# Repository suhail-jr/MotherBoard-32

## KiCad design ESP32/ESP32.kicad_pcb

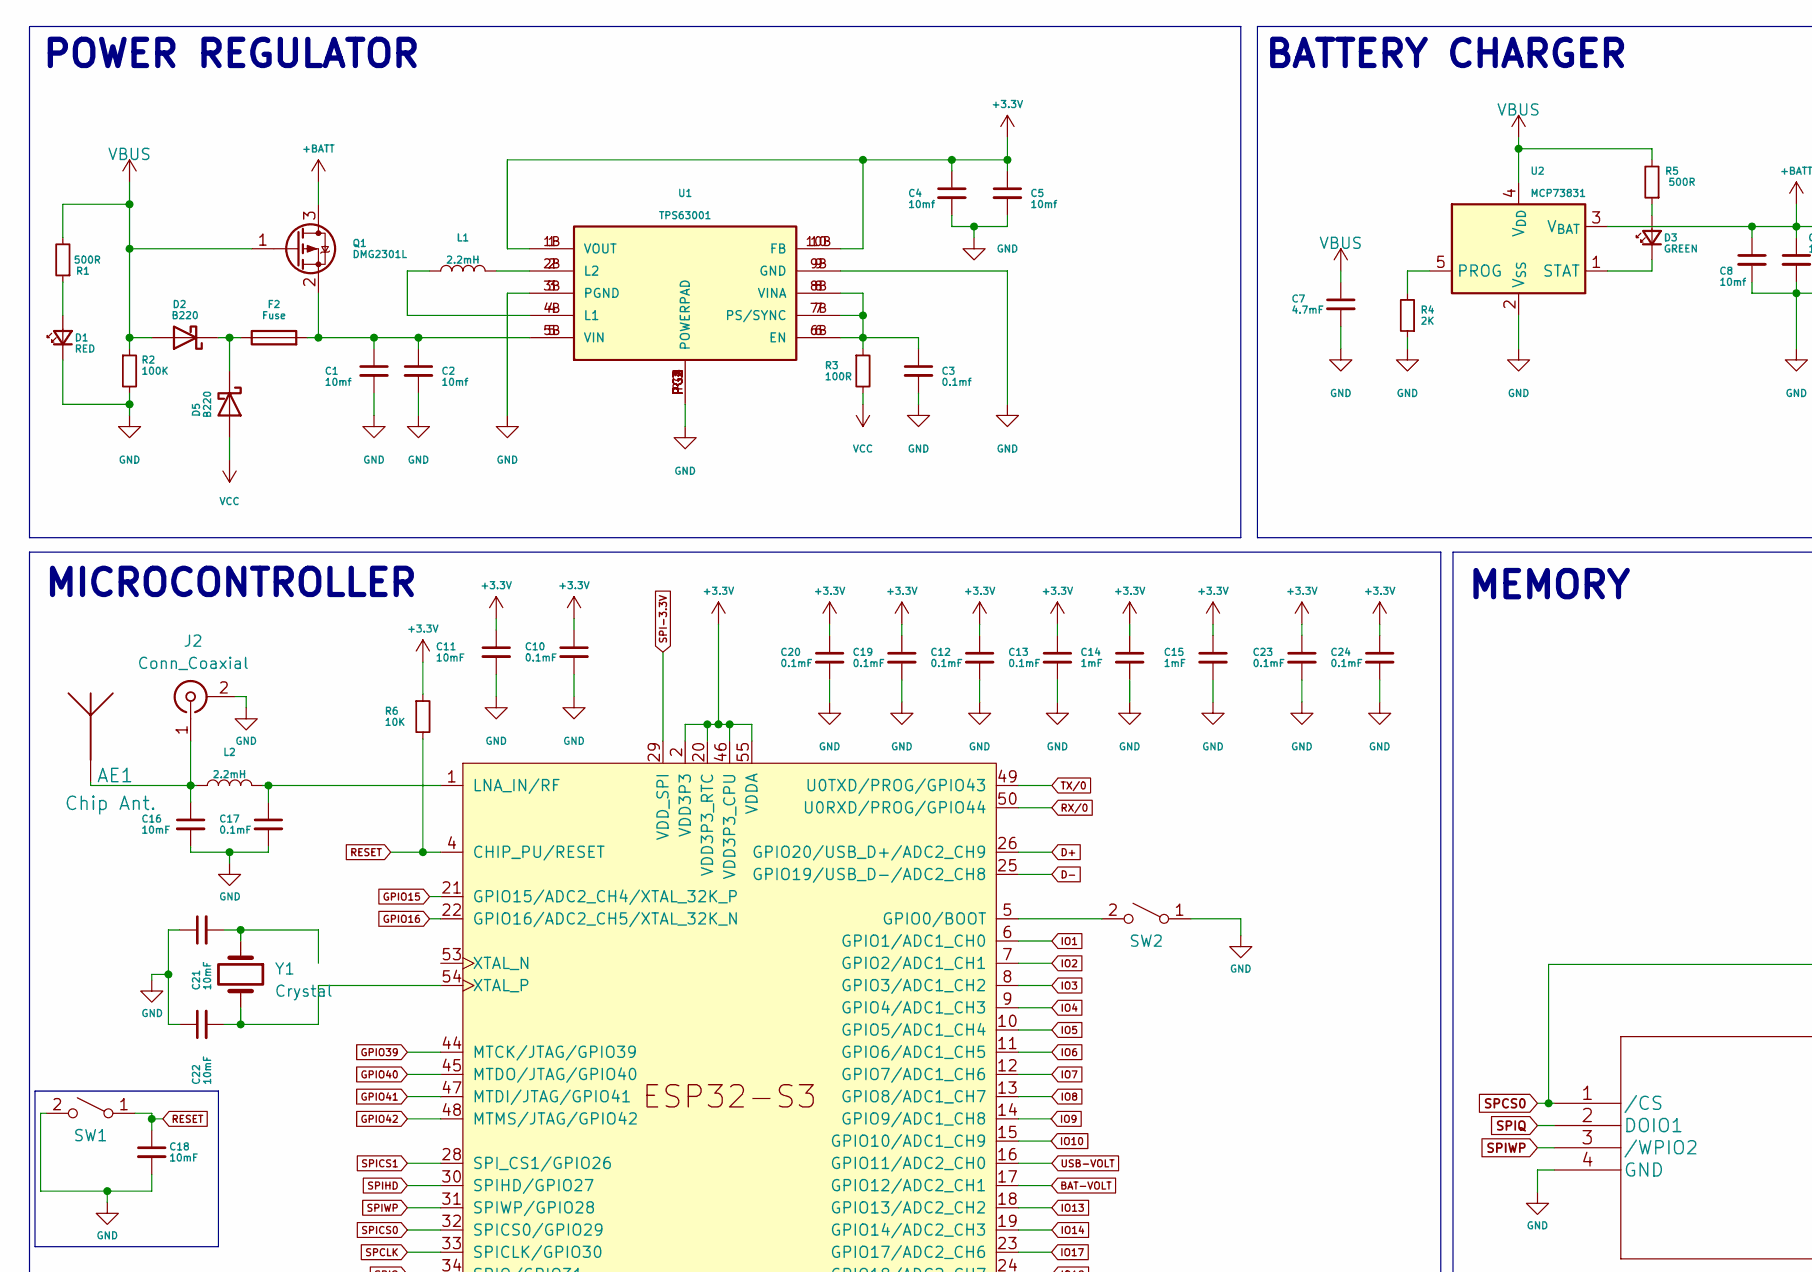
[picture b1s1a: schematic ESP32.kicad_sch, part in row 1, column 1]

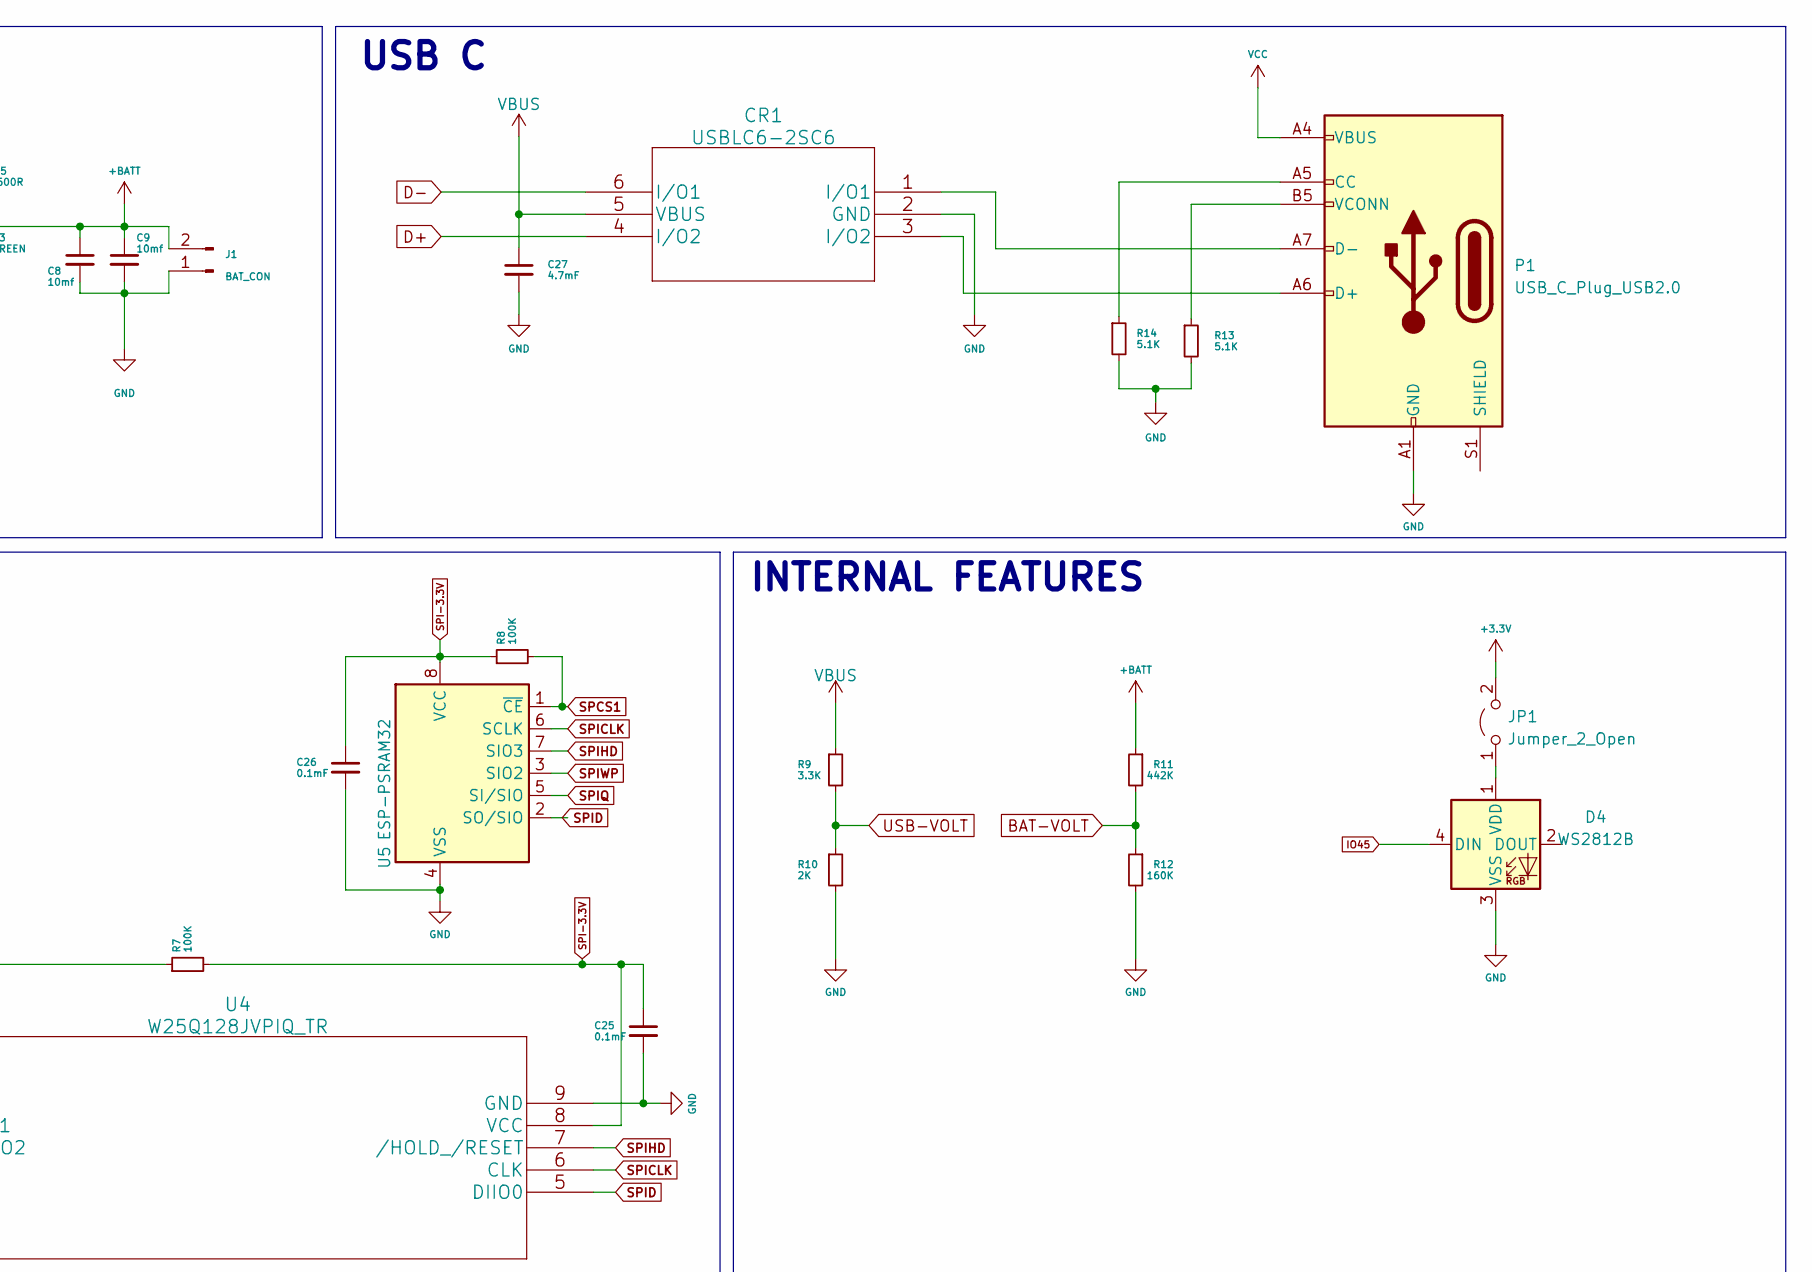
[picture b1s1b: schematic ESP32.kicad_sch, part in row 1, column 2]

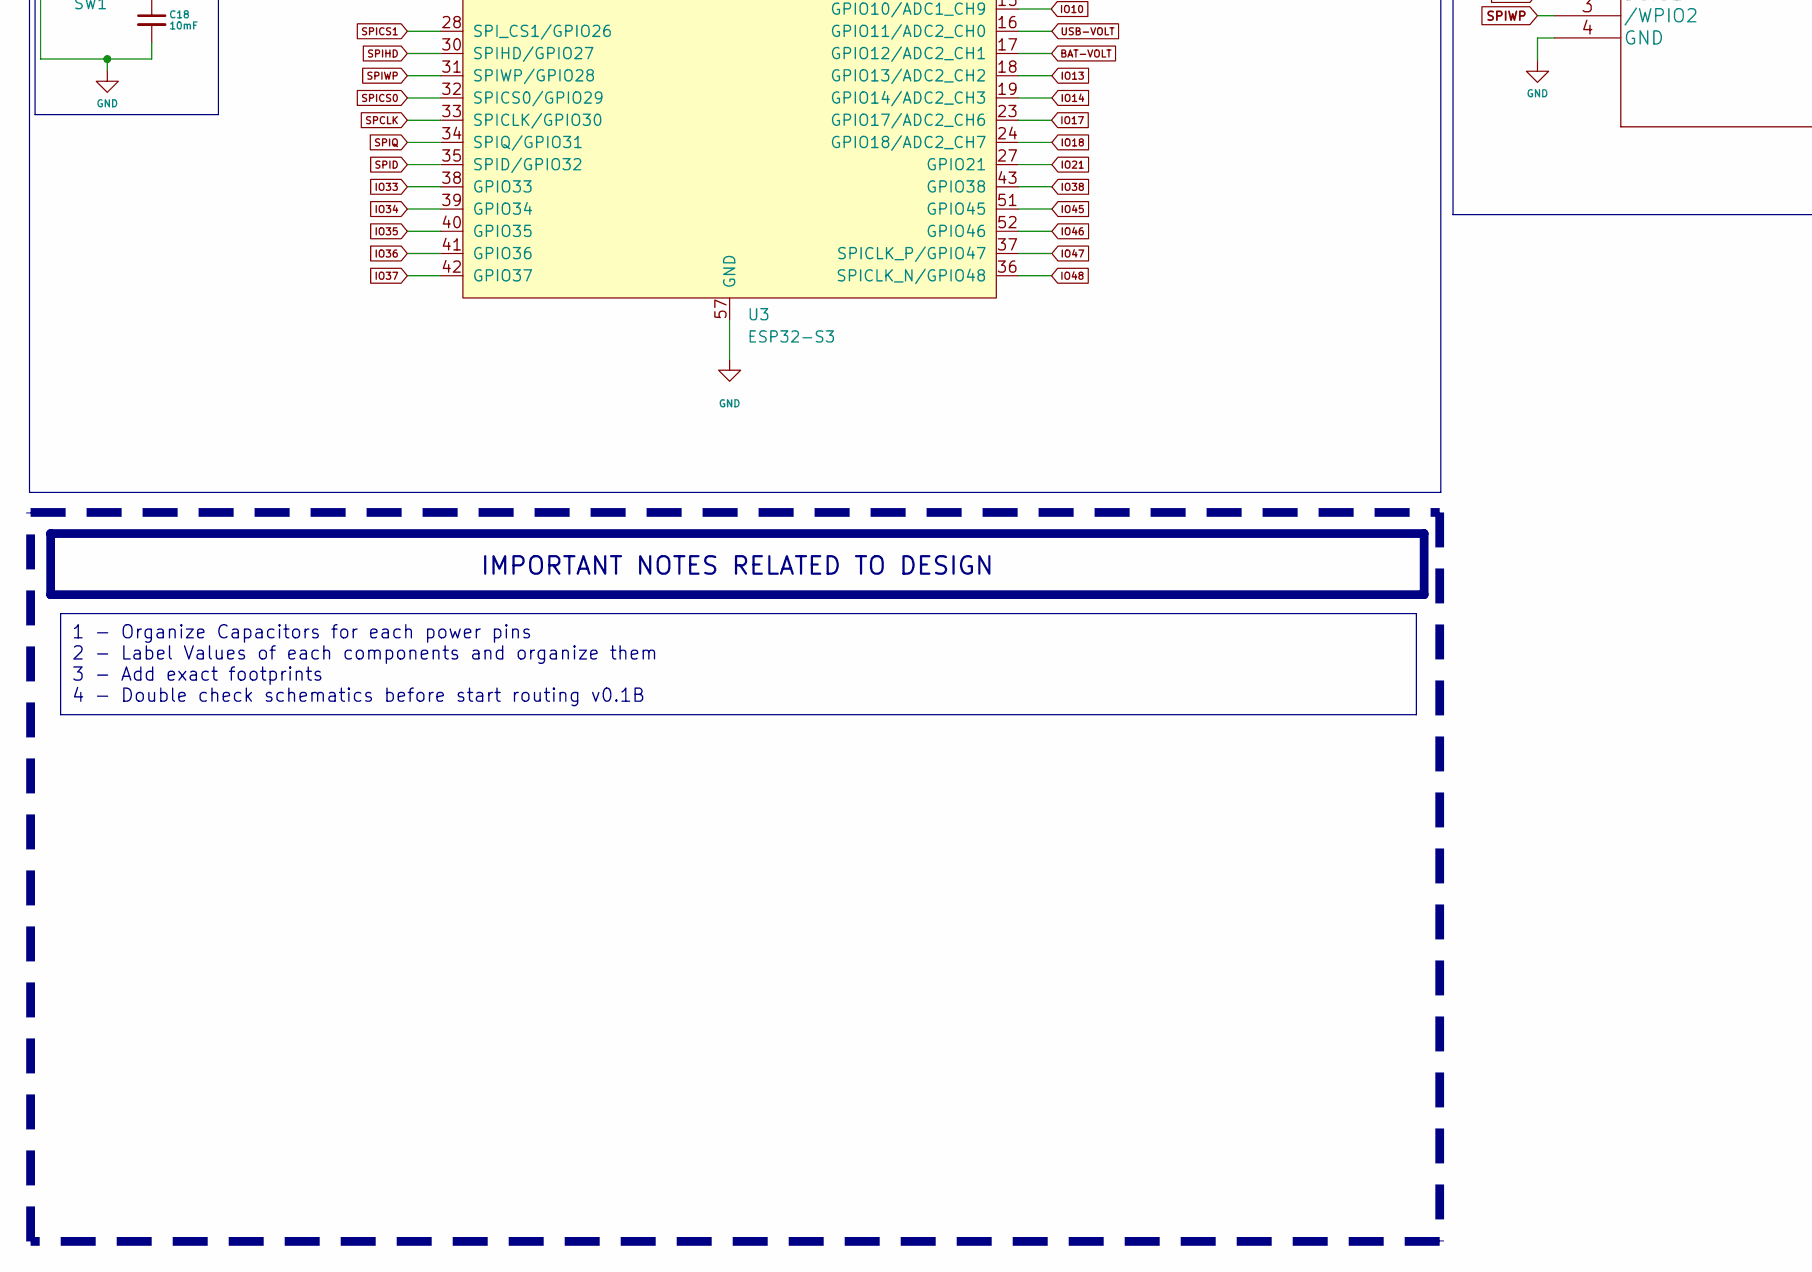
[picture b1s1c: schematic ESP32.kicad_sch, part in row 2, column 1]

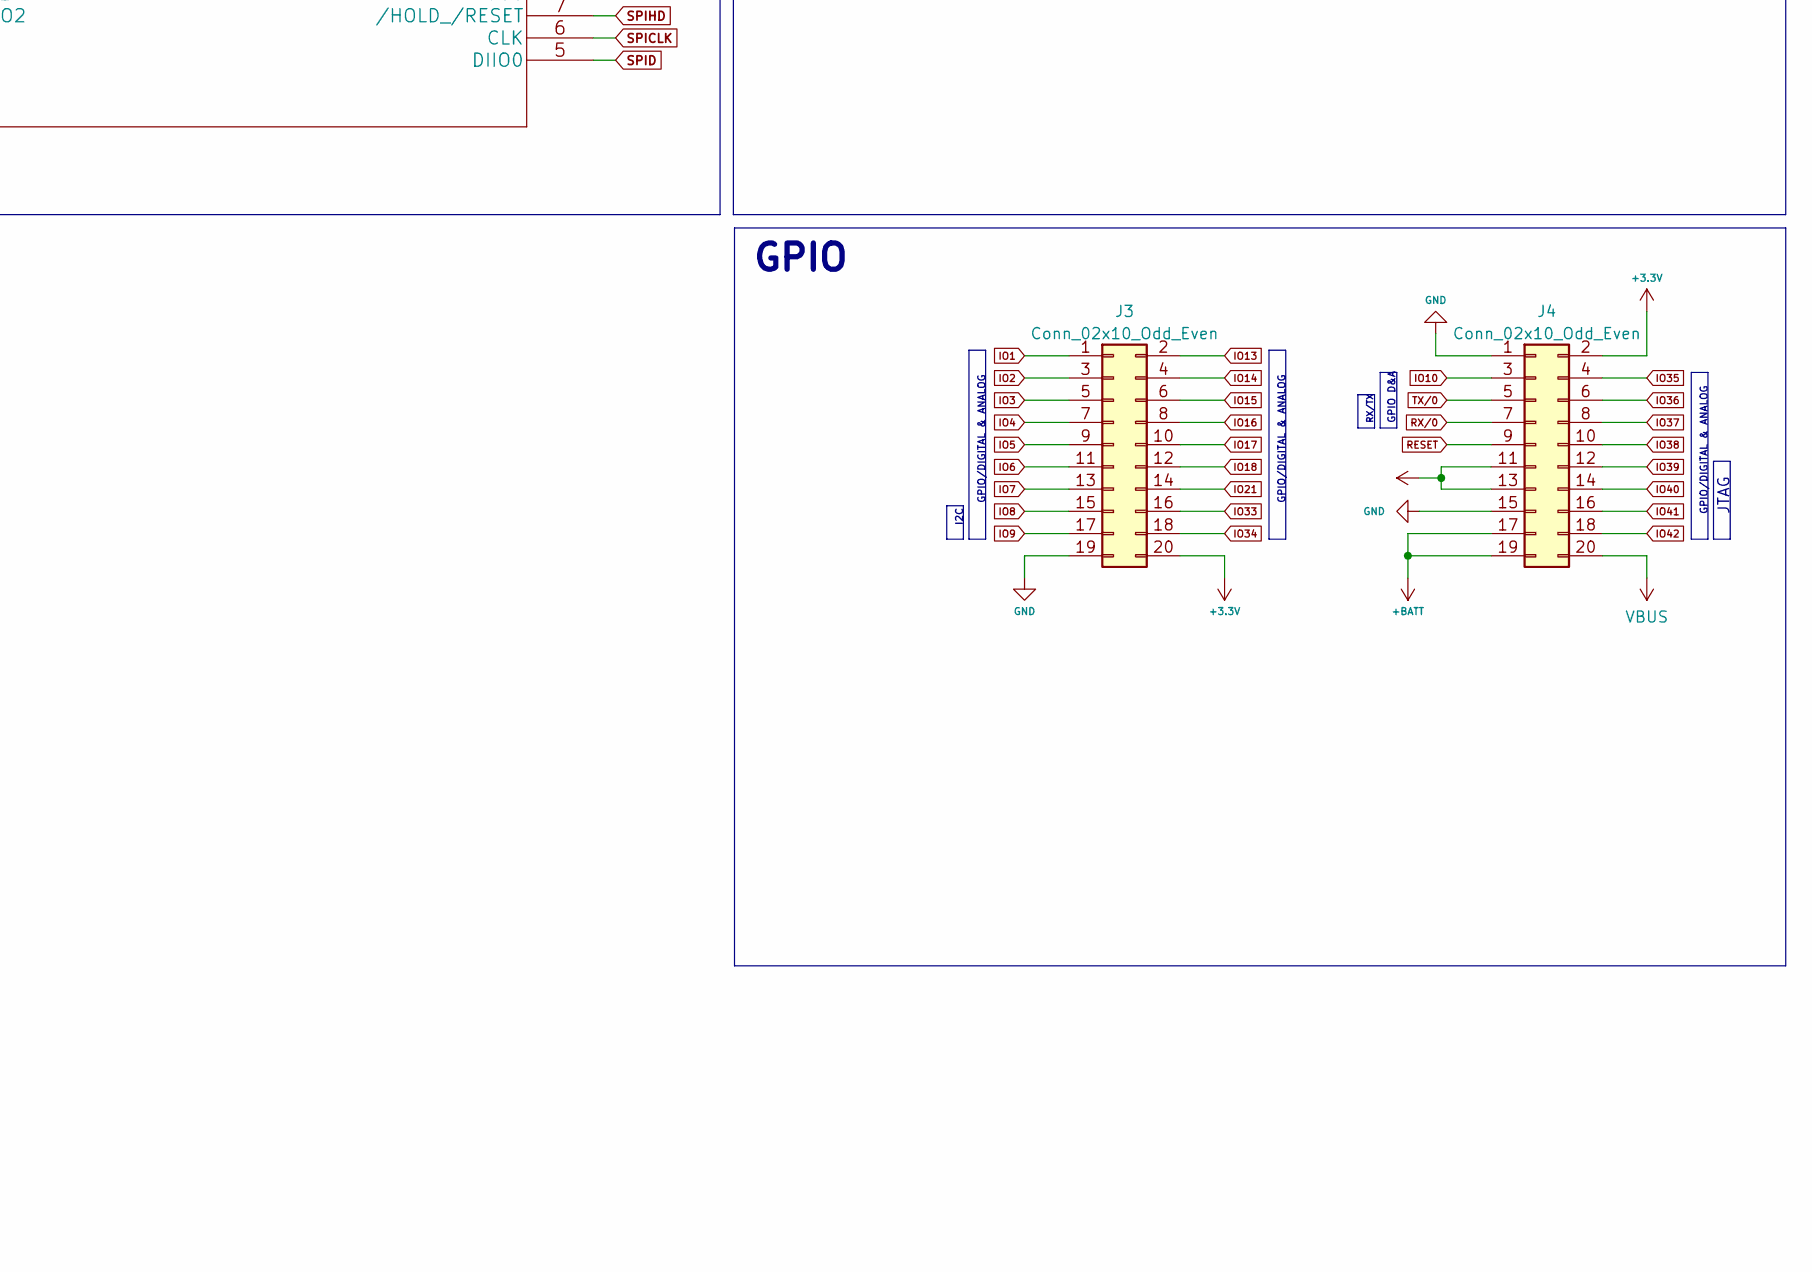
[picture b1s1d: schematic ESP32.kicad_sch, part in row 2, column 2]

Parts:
AE1: Chip Ant.; 2450AT42A100E
C1, C2, C4, C5: 10mf; C_0603_1608Metric
C3: 0.1mf; C_0402_1005Metric
C7: 4.7mF; C_0603_1608Metric
C8, C9: 10mf; C_0805_2012Metric
C10, C12, C13, C17, C19, C20, C23, C24, C25, C26: 0.1mF; C_0402_1005Metric
C11, C16, C18, C21, C22: 10mF; C_0402_1005Metric
C14, C15: 1mF; C_0402_1005Metric
C27: 4.7mF; C_0402_1005Metric
CR1: USBLC6-2SC6
D1: RED; LED_0603_1608Metric
D2, D5: B220; D_SOD-323
D3: GREEN; LED_0603_1608Metric
D4: WS2812B; LED_WS2812B-2020_PLCC4_2.0x2.0mm
F2: Fuse; Fuse_0805_2012Metric_Pad1.15x1.40mm_HandSolder
J1: BAT_CON; JST_SHL_SM02B-SHLS-TF_1x02-1MP_P1.00mm_Horizontal
J2: Conn_Coaxial; U.FL_Molex_MCRF_73412-0110_Vertical
J3, J4: Conn_02x10_Odd_Even; HRS_DF12NB-20DS-0.5V(51)
JP1: Jumper_2_Open; SolderJumper-2_P1.3mm_Open_TrianglePad1.0x1.5mm
L1: 2.2mH; L_0402_1005Metric
L2: 2.2mH; L_0603_1608Metric
P1: USB_C_Plug_USB2.0; MOLEX_2169900003
Q1: DMG2301L; SOT-23
R1, R5: 500R; R_0402_1005Metric
R2, R7, R8: 100K; R_0402_1005Metric
R3: 100R; R_0402_1005Metric
R4, R10: 2K; R_0402_1005Metric
R6: 10K; R_0402_1005Metric
R9: 3.3K; R_0402_1005Metric
R11: 442K; R_0402_1005Metric
R12: 160K; R_0402_1005Metric
R13, R14: 5.1K; R_0402_1005Metric
SW1, SW2: SW_SPST; SW_SKRPACE010
U1: TPS63001
U2: MCP73831; SOT-23-5
U3: ESP32-S3; QFN-56-1EP_7x7mm_P0.4mm_EP5.6x5.6mm
U4: W25Q128JVPIQ_TR; SON127P610X510X80-8N430X340
U5: ESP-PSRAM32; SOIC-8_3.9x4.9mm_P1.27mm
Y1: Crystal; Crystal_SMD_3225-4Pin_3.2x2.5mm

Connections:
+3.3V: C4.1, C5.1, C10.1, C11.1, C12.1, C13.1, C14.1, C15.1, C19.1, C20.1, C23.1, C24.1, J3.20, J4.2, JP1.2 (B), R6.1, U1.1 (VOUT), U1.1B (VOUT), U1.10 (FB), U1.10B (FB), U3.2 (VDD3P3), U3.3 (VDD3P3), U3.20 (VDD3P3_RTC), U3.46 (VDD3P3_CPU), U3.55 (VDDA), U3.56 (VDDA)
+BATT: C8.1, C9.1, J1.2, J4.17, J4.19, Q1.3 (D), R11.1, U2.3 (V_{BAT})
BAT-VOLT: R11.2, R12.1, U3.17 (GPIO12/ADC2_CH1)
D+: CR1.4 (I/O2), U3.26 (GPIO20/USB_D+/ADC2_CH9)
D-: CR1.6 (I/O1), U3.25 (GPIO19/USB_D-/ADC2_CH8)
GND: C1.2, C2.2, C3.2, C4.2, C5.2, C7.2, C8.2, C9.2, C10.2, C11.2, C12.2, C13.2, C14.2, C15.2, C16.2, C17.2, C18.2, C19.2, C20.2, C21.1, C22.1, C23.2, C24.2, C25.2, C26.2, C27.2, CR1.2 (GND), D1.1 (K), D4.3 (VSS), J1.1, J2.2 (Ext), J3.19, J4.1, J4.15, P1.A1 (GND), P1.A12 (GND), P1.B1 (GND), P1.B12 (GND), R2.2, R4.1, R10.2, R12.2, R13.2, R14.2, SW1.2 (B), SW2.1 (A), U1.3 (PGND), U1.3B (PGND), U1.9 (GND), U1.9B (GND), U1.PG (POWERPAD), U1.PG1 (POWERPAD), U1.PG2 (POWERPAD), U1.PG3 (POWERPAD), U1.PG4 (POWERPAD), U2.2 (V_{SS}), U3.57 (GND), U4.4 (GND), U4.9 (GND), U5.4 (VSS)
GPIO15: U3.21 (GPIO15/ADC2_CH4/XTAL_32K_P)
GPIO16: U3.22 (GPIO16/ADC2_CH5/XTAL_32K_N)
GPIO39: U3.44 (MTCK/JTAG/GPIO39)
GPIO40: U3.45 (MTDO/JTAG/GPIO40)
GPIO41: U3.47 (MTDI/JTAG/GPIO41)
GPIO42: U3.48 (MTMS/JTAG/GPIO42)
IO1: J3.1, U3.6 (GPIO1/ADC1_CH0)
IO2: J3.3, U3.7 (GPIO2/ADC1_CH1)
IO3: J3.5, U3.8 (GPIO3/ADC1_CH2)
IO4: J3.7, U3.9 (GPIO4/ADC1_CH3)
IO5: J3.9, U3.10 (GPIO5/ADC1_CH4)
IO6: J3.11, U3.11 (GPIO6/ADC1_CH5)
IO7: J3.13, U3.12 (GPIO7/ADC1_CH6)
IO8: J3.15, U3.13 (GPIO8/ADC1_CH7)
IO9: J3.17, U3.14 (GPIO9/ADC1_CH8)
IO10: J4.3, U3.15 (GPIO10/ADC1_CH9)
IO13: J3.2, U3.18 (GPIO13/ADC2_CH2)
IO14: J3.4, U3.19 (GPIO14/ADC2_CH3)
IO15: J3.6
IO16: J3.8
IO17: J3.10, U3.23 (GPIO17/ADC2_CH6)
IO18: J3.12, U3.24 (GPIO18/ADC2_CH7)
IO21: J3.14, U3.27 (GPIO21)
IO33: J3.16, U3.38 (GPIO33)
IO34: J3.18, U3.39 (GPIO34)
IO35: J4.4, U3.40 (GPIO35)
IO36: J4.6, U3.41 (GPIO36)
IO37: J4.8, U3.42 (GPIO37)
IO38: J4.10, U3.43 (GPIO38)
IO39: J4.12
IO40: J4.14
IO41: J4.16
IO42: J4.18
IO45: D4.4 (DIN), U3.51 (GPIO45)
IO46: U3.52 (GPIO46)
IO47: U3.37 (SPICLK_P/GPIO47)
IO48: U3.36 (SPICLK_N/GPIO48)
unnamed: C3.1, R3.1, U1.6 (EN), U1.6B (EN), U1.7 (PS/SYNC), U1.7B (PS/SYNC), U1.8 (VINA), U1.8B (VINA)
unnamed: C21.2, Y1.1
unnamed: D1.2 (A), R1.1
unnamed: D2.1 (K), D5.1 (K), F2.1
unnamed: D3.2 (A), R5.1
unnamed: D3.1 (K), U2.1 (STAT)
unnamed: D4.1 (VDD), JP1.1 (A)
unnamed: AE1.1, C16.1, J2.1 (In), L2.1
unnamed: L1.1, U1.4 (L1), U1.4B (L1)
unnamed: L1.2, U1.2 (L2), U1.2B (L2)
unnamed: P1.A5 (CC), R14.1
unnamed: CR1.3 (I/O2), P1.A6 (D+)
unnamed: CR1.1 (I/O1), P1.A7 (D-)
unnamed: P1.B5 (VCONN), R13.1
unnamed: C1.1, C2.1, F2.2, Q1.2 (S), U1.5 (VIN), U1.5B (VIN)
unnamed: SW2.2 (B), U3.5 (GPIO0/BOOT)
unnamed: R4.2, U2.5 (PROG)
unnamed: C17.1, L2.2, U3.1 (LNA_IN/RF)
unnamed: C22.2, U3.54 (XTAL_P), Y1.2
RESET: C18.1, J4.9, R6.2, SW1.1 (A), U3.4 (CHIP_PU/RESET)
RX/0: J4.7, U3.50 (U0RXD/PROG/GPIO44)
SPCLK: U3.33 (SPICLK/GPIO30)
SPCS0: R7.1, U4.1 (/CS)
SPCS1: R8.2, U5.1 (~CE)
SPI-3.3V: C25.1, C26.1, R7.2, R8.1, U3.29 (VDD_SPI), U4.8 (VCC), U5.8 (VCC)
SPICLK: U4.6 (CLK), U5.6 (SCLK)
SPICS0: U3.32 (SPICS0/GPIO29)
SPICS1: U3.28 (SPI_CS1/GPIO26)
SPID: U3.35 (SPID/GPIO32), U4.5 (DIIO0), U5.2 (SO/SIO)
SPIHD: U3.30 (SPIHD/GPIO27), U4.7 (/HOLD_/RESET), U5.7 (SIO3)
SPIQ: U3.34 (SPIQ/GPIO31), U4.2 (DOIO1), U5.5 (SI/SIO)
SPIWP: U3.31 (SPIWP/GPIO28), U4.3 (/WPIO2), U5.3 (SIO2)
TX/0: J4.5, U3.49 (U0TXD/PROG/GPIO43)
USB-VOLT: R9.2, R10.1, U3.16 (GPIO11/ADC2_CH0)
VBUS: C7.1, C27.1, CR1.5 (VBUS), D2.2 (A), J4.20, Q1.1 (G), R1.2, R2.1, R5.2, R9.1, U2.4 (V_{DD})
VCC: D5.2 (A), J4.11, J4.13, P1.A4 (VBUS), P1.A9 (VBUS), P1.B4 (VBUS), P1.B9 (VBUS), R3.2

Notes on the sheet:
1 - Organize Capacitors for each power pins 2 - Label Values of each components and organize them 3 - Add exact footprints 4 - Double check schematics before start routing v0.1B
RX/TX
GPIO/DIGITAL & ANALOG
GPIO
USB C
POWER REGULATOR
INTERNAL FEATURES
MEMORY
GPIO D&A
IMPORTANT NOTES RELATED TO DESIGN
BATTERY CHARGER
JTAG
MICROCONTROLLER
I2C

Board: 2 copper layers, 65 parts (2 on the bottom side), 61 nets, no tracks yet.

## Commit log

2023-03-13 no message
2023-03-14 added power regulator and battery charger
2023-03-15 addes the memory chips
2023-03-16 Added Gpio and remaing cicuits
2023-03-16 added notes
2023-03-17 added footprints
2023-03-18 Components are organized

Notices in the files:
parts and their libraries:
Copyright 2021 Accelerated Designs. All rights reserved.
